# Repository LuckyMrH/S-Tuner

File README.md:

S-Tuner
=======

Stroboscopic Guitar Tuner based on the TI MSP-430

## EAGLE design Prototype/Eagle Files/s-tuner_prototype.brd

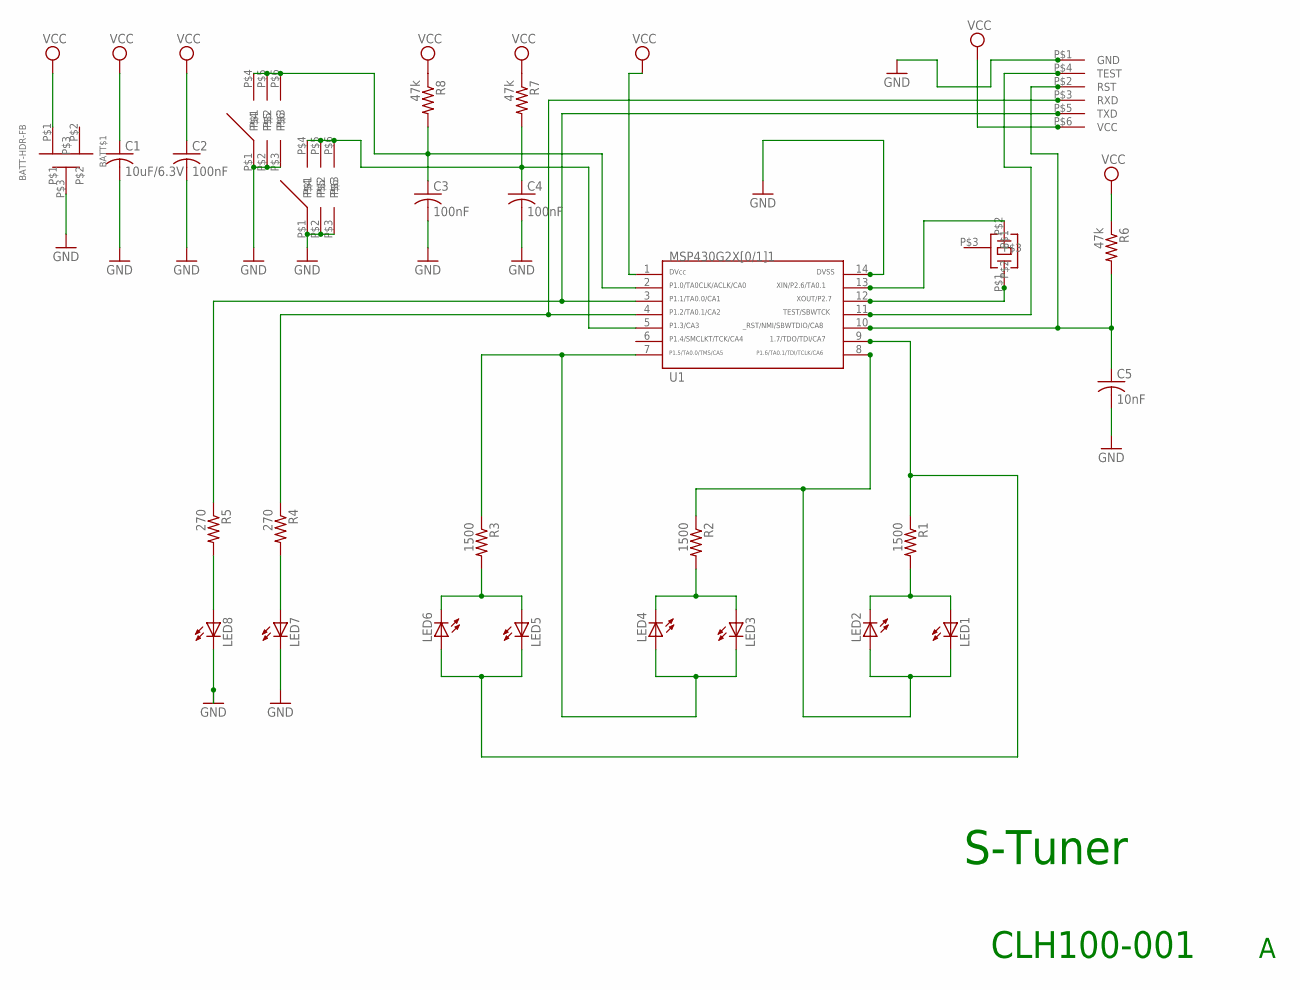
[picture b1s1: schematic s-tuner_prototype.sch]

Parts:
BATT1: BATT1; BATT-HDR-FB
C1: 10uF/6.3V; C1206K
C2, C3, C4: 100nF; C0603
C5: 10nF; C0603
LED1, LED2, LED3, LED4, LED5, LED6: LEDSML0805; SML0805
LED7, LED8: LED3MM
R1, R2, R3: 1500; R0603
R4, R5: 270; R0603
R6, R7, R8: 47k; R0603
SW1, SW2: POLYCASE_FINGER_TRACE
U1: G2X[0/1]1---PW14; PW14
U2: MICROCRYSTAL_32K
U$3: PROGRAMMING_HEADER

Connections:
GND: BATT1.P$3, C1.2, C2.2, C3.2, C4.2, C5.2, LED7.K (C), LED8.K (C), SW1.P$1, SW1.P$2, SW1.P$3, SW2.P$1, SW2.P$2, SW2.P$3, U1.14, U$3.P$1 (GND)
unnamed: U1.12, U2.P$1
unnamed: C5.1, R6.2, U1.10, U$3.P$2 (RST)
unnamed: LED1.C, LED2.A, R2.1, U1.8
unnamed: U1.13, U2.P$2
unnamed: LED5.C, LED6.A, R1.1, U1.9
unnamed: C3.1, R8.2, SW1.P$4, SW1.P$5, SW1.P$6, U1.2
unnamed: LED5.A, LED6.C, R3.2
unnamed: LED3.C, LED4.A, R3.1, U1.7
unnamed: R4.1, U1.4, U$3.P$3 (RXD)
unnamed: LED1.A, LED2.C, R1.2
unnamed: LED7.A, R4.2
unnamed: R5.1, U1.3, U$3.P$5 (TXD)
unnamed: LED3.A, LED4.C, R2.2
unnamed: U1.11, U$3.P$4 (TEST)
unnamed: C4.1, R7.2, SW2.P$4, SW2.P$5, SW2.P$6, U1.5
unnamed: LED8.A, R5.2
VCC: BATT1.P$1, C1.1, C2.1, R6.1, R7.1, R8.1, U1.1, U$3.P$6 (VCC)

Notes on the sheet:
S-Tuner
CLH100-001

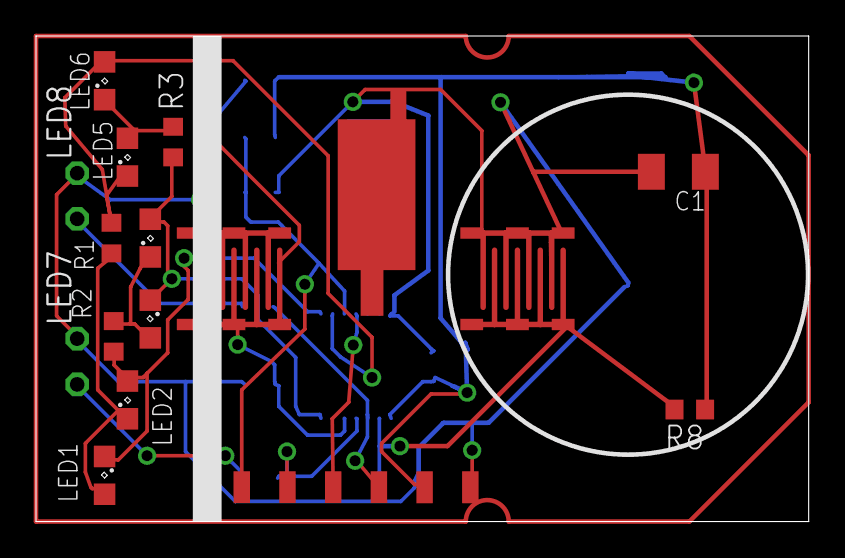
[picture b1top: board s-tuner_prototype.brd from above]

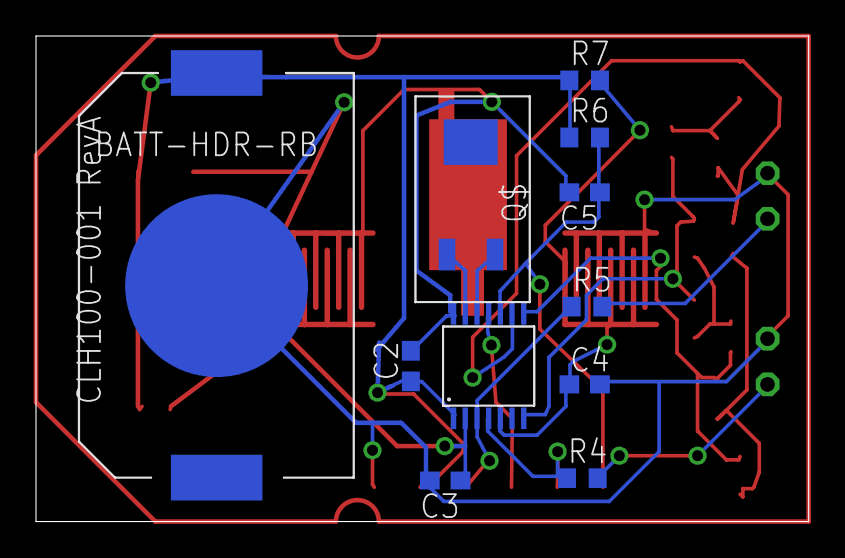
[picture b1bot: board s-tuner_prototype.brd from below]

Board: 2 copper layers, 42.9 x 27.0 mm, 27 parts (11 on the bottom side), 18 nets.

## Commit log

2020-07-22 Add files via upload
    All files for S-Tuner project
